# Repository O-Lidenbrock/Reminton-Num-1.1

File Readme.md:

The Remington #2 was the first typewriter with "macros" - it typed lowercase or uppercase based on whether the user was holding the Shift key. This modern, battery powered keyboard is much smaller and more portable than that original typewriter, but has lost a key. Since this layout is missing the right Shift, it's a version before the Remington #2 - the Remington #1.1

I built this to have a keyboard to use in college. Since it's battery powered, I can throw it in my backpack and use it wherever I'm studying.

> Resubmit Changes:
>
> * Designed a new base to look like a typewriter
> * Found a set of keycaps in a color scheme closer to a typewriter

### BOM

| Item                    | Qty | Price USD (including shipping) | Link                                                                 |
|-------------------------|-----|-------------------------------|----------------------------------------------------------------------|
| Gateron Red Switches x65 | 1   | $21.34                       | https://www.aliexpress.us/item/3256805364014141.html       |
| Keycaps x65             | 1   | $13.50                        | https://www.aliexpress.us/item/3256805435936202.html       |
| PCB                     | 1   | $29.81                        | JLCPCB                                                      |
| Diodes x65              | 1   | $1.45                         | https://www.aliexpress.us/item/3256803242364455.html        |
| Nice!Nano V2            | 1   | $25.00                        | https://typeractive.xyz/products/nice-nano                  |
| Stabilizers             | 1   | $2.96                         | https://www.aliexpress.us/item/3256802930868859.html        |
| 3D Printed Case         | 1   | Free                          | Self-printed                                                |
| 601230 3.7V 200mAh Battery | 1 | 12.39                        | https://www.aliexpress.us/item/2251832650224851.html        |
| M3 Heatset Inserts      | 1   | $4.62                         | https://www.aliexpress.us/item/3256804442999990.html        |
| Nano Headers/Sockets    | 1   | Free                          | From my own stock                                           |                     
Total: $111.07 USD

### Schematic

### PCB

### CAD
Base

Plate

### Key Layout

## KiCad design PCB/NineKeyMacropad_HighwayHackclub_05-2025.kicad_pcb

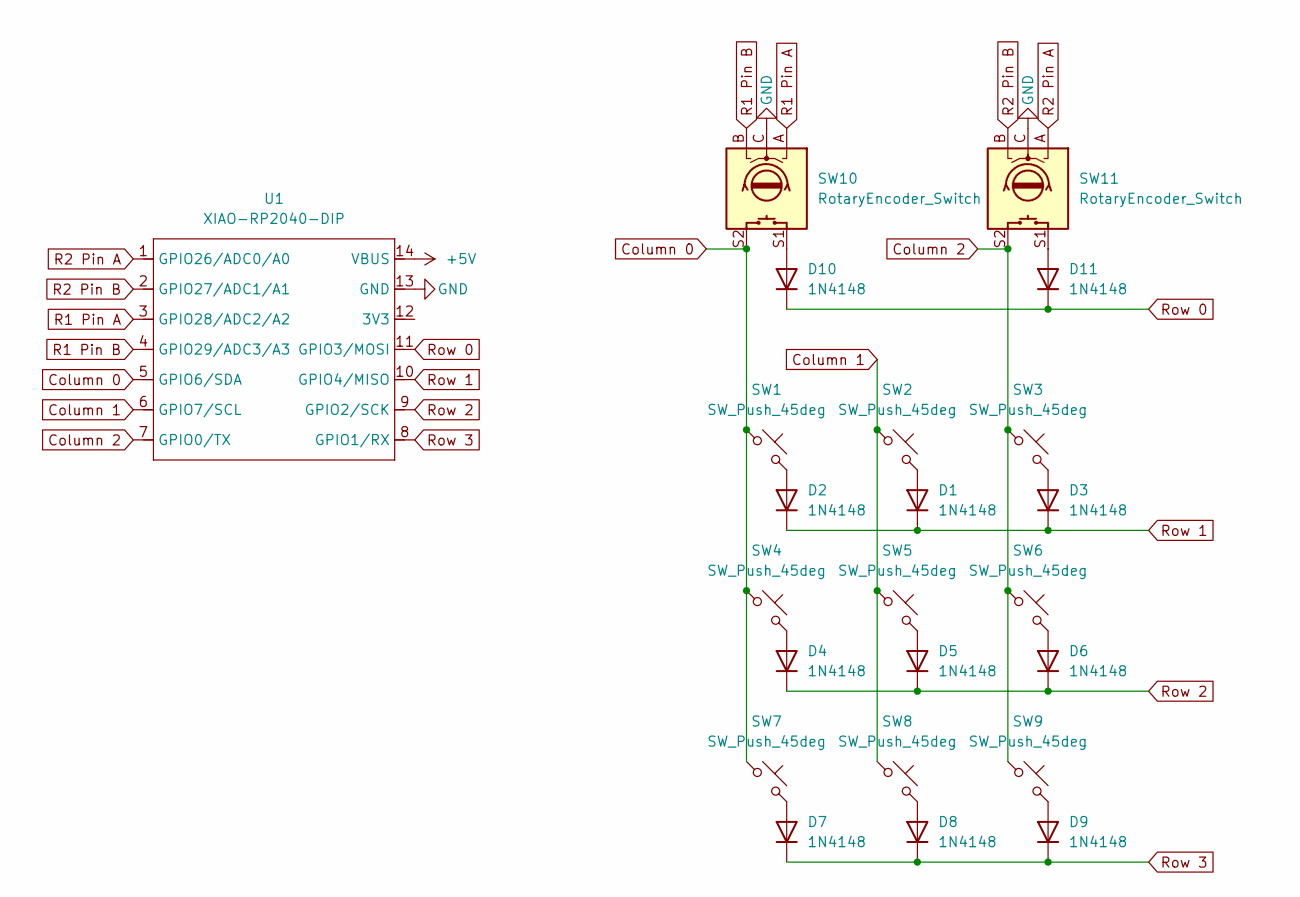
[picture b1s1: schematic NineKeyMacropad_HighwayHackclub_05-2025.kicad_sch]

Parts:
D1, D2, D3, D4, D5, D6, D7, D8, D9, D10, D11: 1N4148; D_DO-35_SOD27_P7.62mm_Horizontal
SW1, SW2, SW3, SW4, SW5, SW6, SW7, SW8, SW9: SW_Push_45deg; SW_Cherry_MX_1.00u_PCB
SW10, SW11: RotaryEncoder_Switch; RotaryEncoder_Alps_EC11E-Switch_Vertical_H20mm
U1: XIAO-RP2040-DIP

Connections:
+5V: U1.14 (VBUS)
Column 0: SW1.1, SW4.1, SW7.1, SW10.S2, U1.5 (GPIO6/SDA)
Column 1: SW2.1, SW5.1, SW8.1, U1.6 (GPIO7/SCL)
Column 2: SW3.1, SW6.1, SW9.1, SW11.S2, U1.7 (GPIO0/TX)
GND: SW10.C, SW11.C, U1.13 (GND)
unnamed: D1.2 (A), SW2.2
unnamed: D2.2 (A), SW1.2
unnamed: D3.2 (A), SW3.2
unnamed: D4.2 (A), SW4.2
unnamed: D5.2 (A), SW5.2
unnamed: D6.2 (A), SW6.2
unnamed: D7.2 (A), SW7.2
unnamed: D8.2 (A), SW8.2
unnamed: D9.2 (A), SW9.2
unnamed: D10.2 (A), SW10.S1
unnamed: D11.2 (A), SW11.S1
R1 Pin A: SW10.A, U1.3 (GPIO28/ADC2/A2)
R1 Pin B: SW10.B, U1.4 (GPIO29/ADC3/A3)
R2 Pin A: SW11.A, U1.1 (GPIO26/ADC0/A0)
R2 Pin B: SW11.B, U1.2 (GPIO27/ADC1/A1)
Row 0: D10.1 (K), D11.1 (K), U1.11 (GPIO3/MOSI)
Row 1: D1.1 (K), D2.1 (K), D3.1 (K), U1.10 (GPIO4/MISO)
Row 2: D4.1 (K), D5.1 (K), D6.1 (K), U1.9 (GPIO2/SCK)
Row 3: D7.1 (K), D8.1 (K), D9.1 (K), U1.8 (GPIO1/RX)

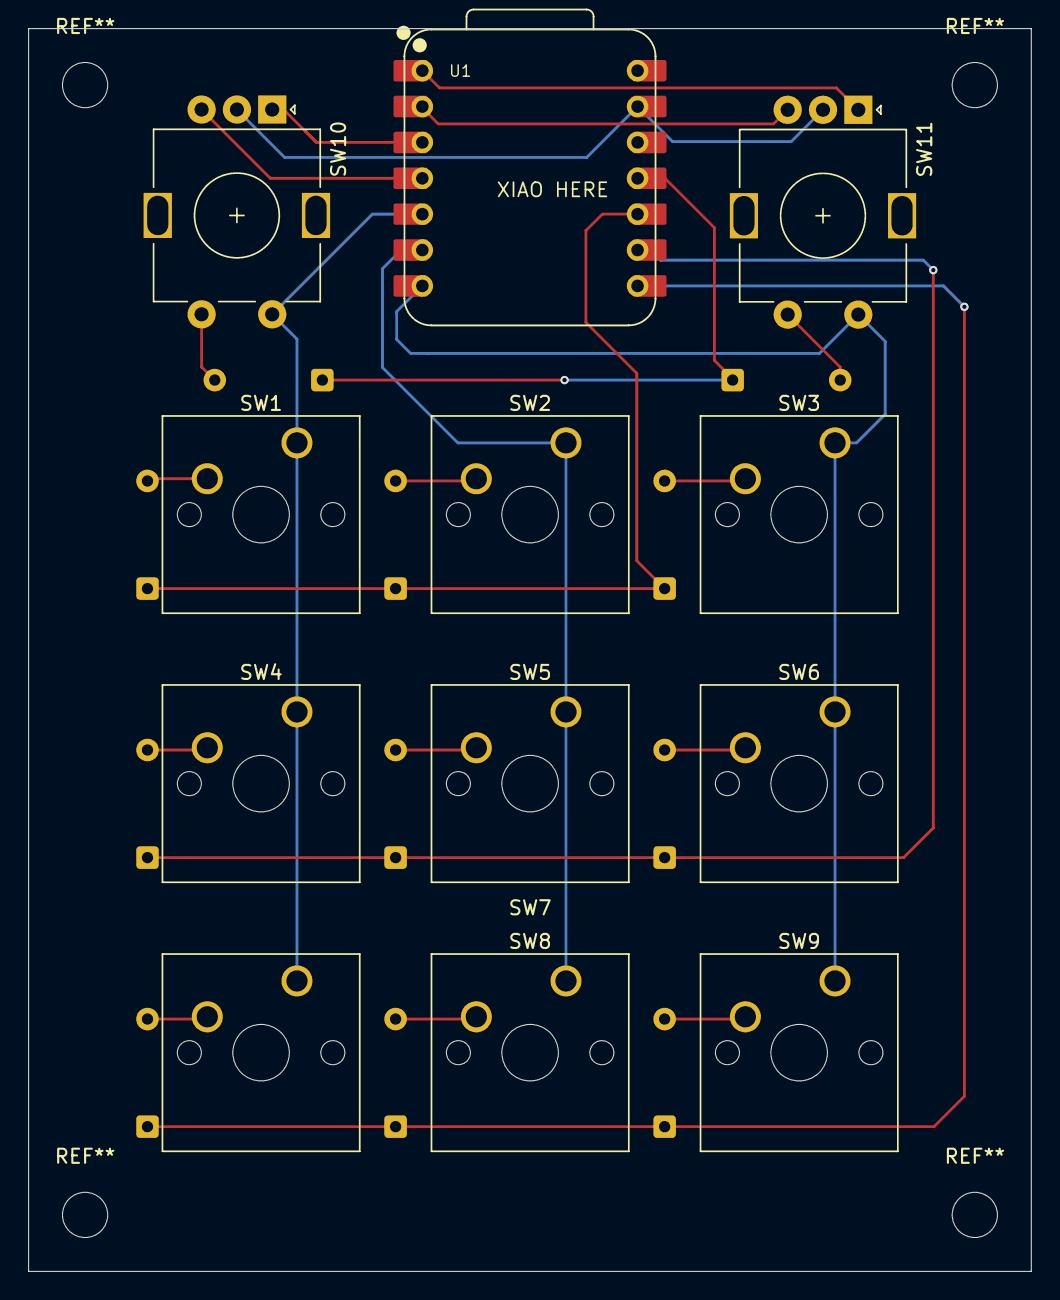
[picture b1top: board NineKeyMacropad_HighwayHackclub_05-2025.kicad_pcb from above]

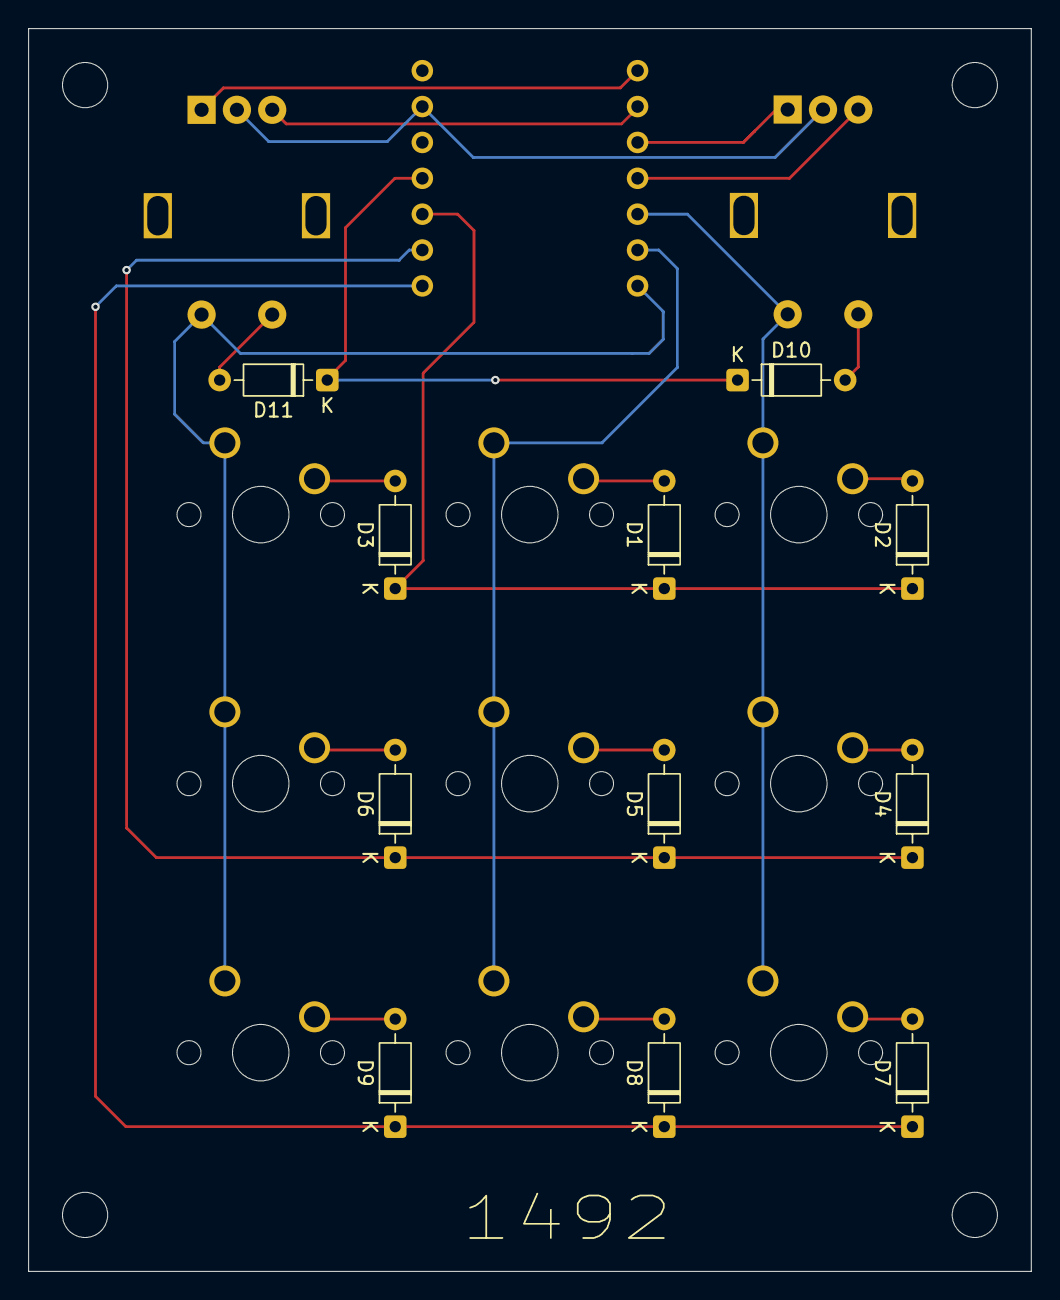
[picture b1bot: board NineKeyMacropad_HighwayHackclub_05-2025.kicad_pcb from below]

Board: 2 copper layers, 71.0 x 88.0 mm, 23 parts (11 on the bottom side), 23 nets.

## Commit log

2025-07-13 first entries
2025-07-13 delete journal entries
    I journaled in the wrong repo
2025-07-13 Journal Today
2025-07-19 Add description to Readme
2025-07-19 Update Journal for 7_19_2025
2025-07-19 Add header to journal
2025-07-19 Update Journal 7_19_2025 second time
2025-07-21 Journal entries 7_20_2025
2025-07-23 Started BOM
2025-07-23 Fix table
2025-07-28 Add step files for keyboard components
2025-07-28 Update BOM
2025-07-28 Update Journal
2025-07-28 Add production files
2025-07-28 Update Journal.md with total time
2025-07-28 Write the Firmware
2025-07-28 Update TIme
2025-07-28 Add a purpose for the project
2025-07-28 Add STEP file (zipped bc too large for github)
2025-07-29 Add Headers (Free) to BOM for clarity
2025-07-29 Update BOM.csv with Headers (Free) for clarity
2025-08-01 Added new case
2025-08-01 Journal the case change
2025-08-03 Fix Journal Images
2025-08-09 video citation
2025-08-09 Base + Plate for final review
2025-08-09 Final CAD
2025-08-15 updated Readme and Journal for V4 build
2025-08-15 Updated production files with Base V4
2025-08-15 trying to update CAD
2025-09-23 priced out board assembly (just the diodes)
2025-09-23 caught up Journal and BOM so I can start ordering parts
2025-09-23 update total time
2025-09-24 Update BOM.csv with new headers
2025-10-21 Update Journal w/ build process
2025-10-21 add uf2 file
2025-10-22 completed the keyboard - update the journal
